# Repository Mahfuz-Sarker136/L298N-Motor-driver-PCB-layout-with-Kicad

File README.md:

# L298N-Motor-driver-PCB-layout-with-Kicad
A custom, dual-layer L298N Motor Driver PCB module optimized for Robotics,Arduino or ESP-32 project
# Custom L298N Motor Driver PCB Module with 5V Regulator

Alhamdulillah, I have completed the design and layout of this custom, high-current 2-layer Motor Driver PCB. This module is specifically optimized for robotics, line-follower robotics applications where robust power management and noise reduction are critical.

## 🚀 Key Features & Specifications

* **H-Bridge Driver:** Utilizes the L298N multi-watt IC to control high-current DC motors.
* **Ground Plane (GND Shielding):** Implemented solid copper pours on  Bottom (B.Cu) layers. This creates an electronic shield that minimizes PWM switching noise and electromagnetic interference (EMI).
* **Advanced Via Stitching:** Strategically placed via arrays/stitching across the board to interconnect the top and bottom ground planes, ensuring a solid, continuous, and low-impedance current return path.
* **Onboard Power Supply:** Integrated an L7805 voltage regulator with decoupling capacitors to step down the motor voltage and provide a clean, stable +5V output for microcontrollers (like ESP32/Arduino) and sensors.
* **Flyback Protection:** Features SS34 SMD Schottky diodes (3A rated) to protect the driver IC from back-EMF inductive voltage spikes generated by DC motors.
* **Heavy-Duty Power Traces:** Power and motor output lines are designed with ultra-wide traces (up to 2.0 mm) to support high current without overheating or causing voltage drops.

## 🛠️ Design Tools & Workflow

* **EDA Software:** KiCad 9.0
* **Manufacturing Standards:** Fully compliant with 2-layer PCB design rules (DRC cleared), customized thermal reliefs for safe soldering, and optimal trace clearance settings.

---
*Feel free to explore the design files, fork this repository, or reach out if you have any feedback or questions regarding the hardware architecture!*

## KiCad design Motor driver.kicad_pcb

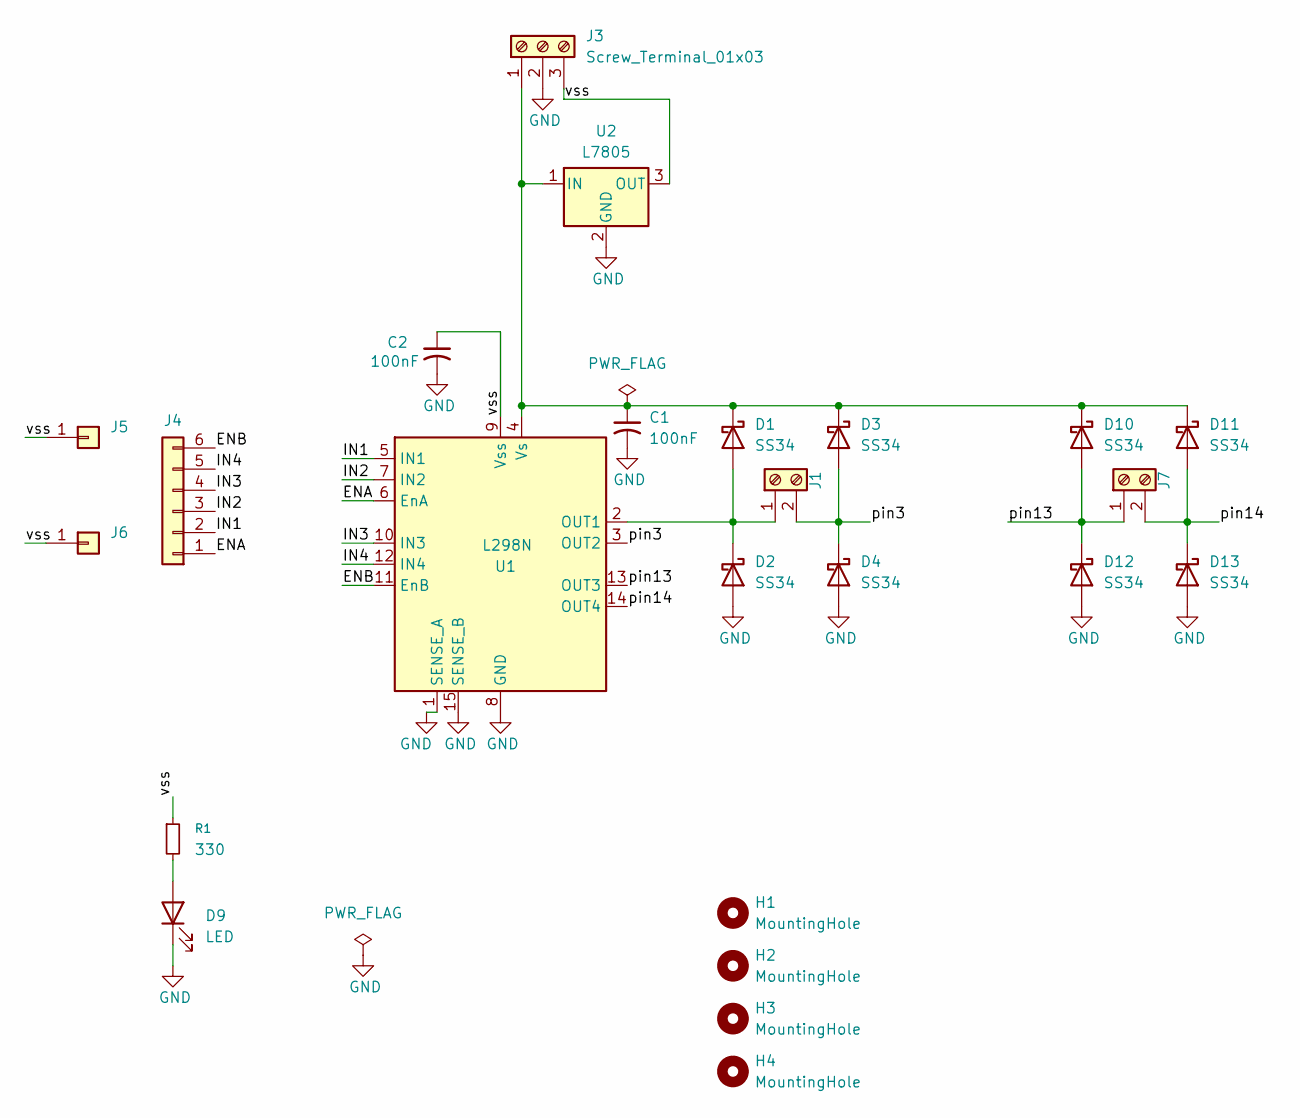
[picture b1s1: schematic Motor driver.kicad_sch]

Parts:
C1, C2: 100nF; CP_Elec_8x10
D1, D2, D3, D4, D10, D11, D12, D13: SS34; D_SMA
D9: LED; LED_0201_0603Metric
H1, H2, H3, H4: MountingHole; MountingHole_2.1mm
J1, J7: Screw_Terminal_01x02; TerminalBlock_MaiXu_MX126-5.0-02P_1x02_P5.00mm
J3: Screw_Terminal_01x03; TerminalBlock_MaiXu_MX126-5.0-03P_1x03_P5.00mm
J4: Conn_01x06; PinHeader_1x06_P2.54mm_Vertical
J5, J6: Conn_01x01; PinHeader_1x01_P2.54mm_Vertical
R1: 330; R_0201_0603Metric
U1: L298N; TO-220-15_P2.54x5.08mm_StaggerOdd_Lead4.58mm_Vertical
U2: L7805; TO-252-3_TabPin2

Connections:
/ENA: J4.1, U1.6 (EnA)
/ENB: J4.6, U1.11 (EnB)
/IN1: J4.2, U1.5 (IN1)
/IN2: J4.3, U1.7 (IN2)
/IN3: J4.4, U1.10 (IN3)
/IN4: J4.5, U1.12 (IN4)
/pin3: D3.2 (A), D4.1 (K), J1.2, U1.3 (OUT2)
/pin13: D10.2 (A), D12.1 (K), J7.1, U1.13 (OUT3)
/pin14: D11.2 (A), D13.1 (K), J7.2, U1.14 (OUT4)
/vss: C2.1, J3.3, J5.1, J6.1, R1.1, U1.9 (Vss), U2.3 (OUT)
GND: C1.2, C2.2, D2.2 (A), D4.2 (A), D9.1 (K), D12.2 (A), D13.2 (A), J3.2, U1.1 (SENSE_A), U1.8 (GND), U1.15 (SENSE_B), U2.2 (GND)
unnamed: D1.2 (A), D2.1 (K), J1.1, U1.2 (OUT1)
unnamed: C1.1, D1.1 (K), D3.1 (K), D10.1 (K), D11.1 (K), J3.1, U1.4 (Vs), U2.1 (IN)
unnamed: D9.2 (A), R1.2

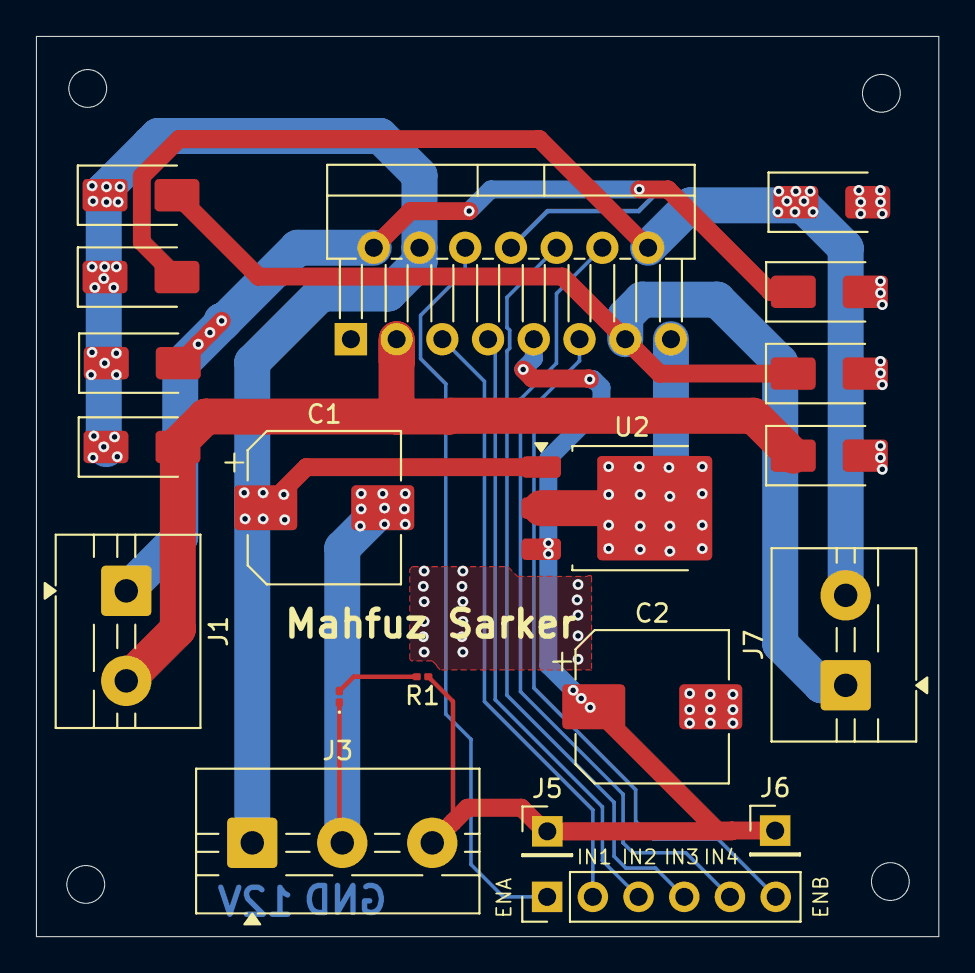
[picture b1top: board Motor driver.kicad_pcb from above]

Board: 2 copper layers, 50.1 x 50.0 mm, 24 parts (0 on the bottom side), 14 nets.
